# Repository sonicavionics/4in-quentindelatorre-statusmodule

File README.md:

# Quentin Dela Torre - Status Module

---

<div align="center">
  <div>

    <p><em>3D Render</em></p>
  </div>
  <br>

  <div>
    <br>
    <p><em>Schematic</em></p>
  </div>
  <br>
  
  <div>
    
    <br>
    <em>Footprint</em>
  </div>
</div>

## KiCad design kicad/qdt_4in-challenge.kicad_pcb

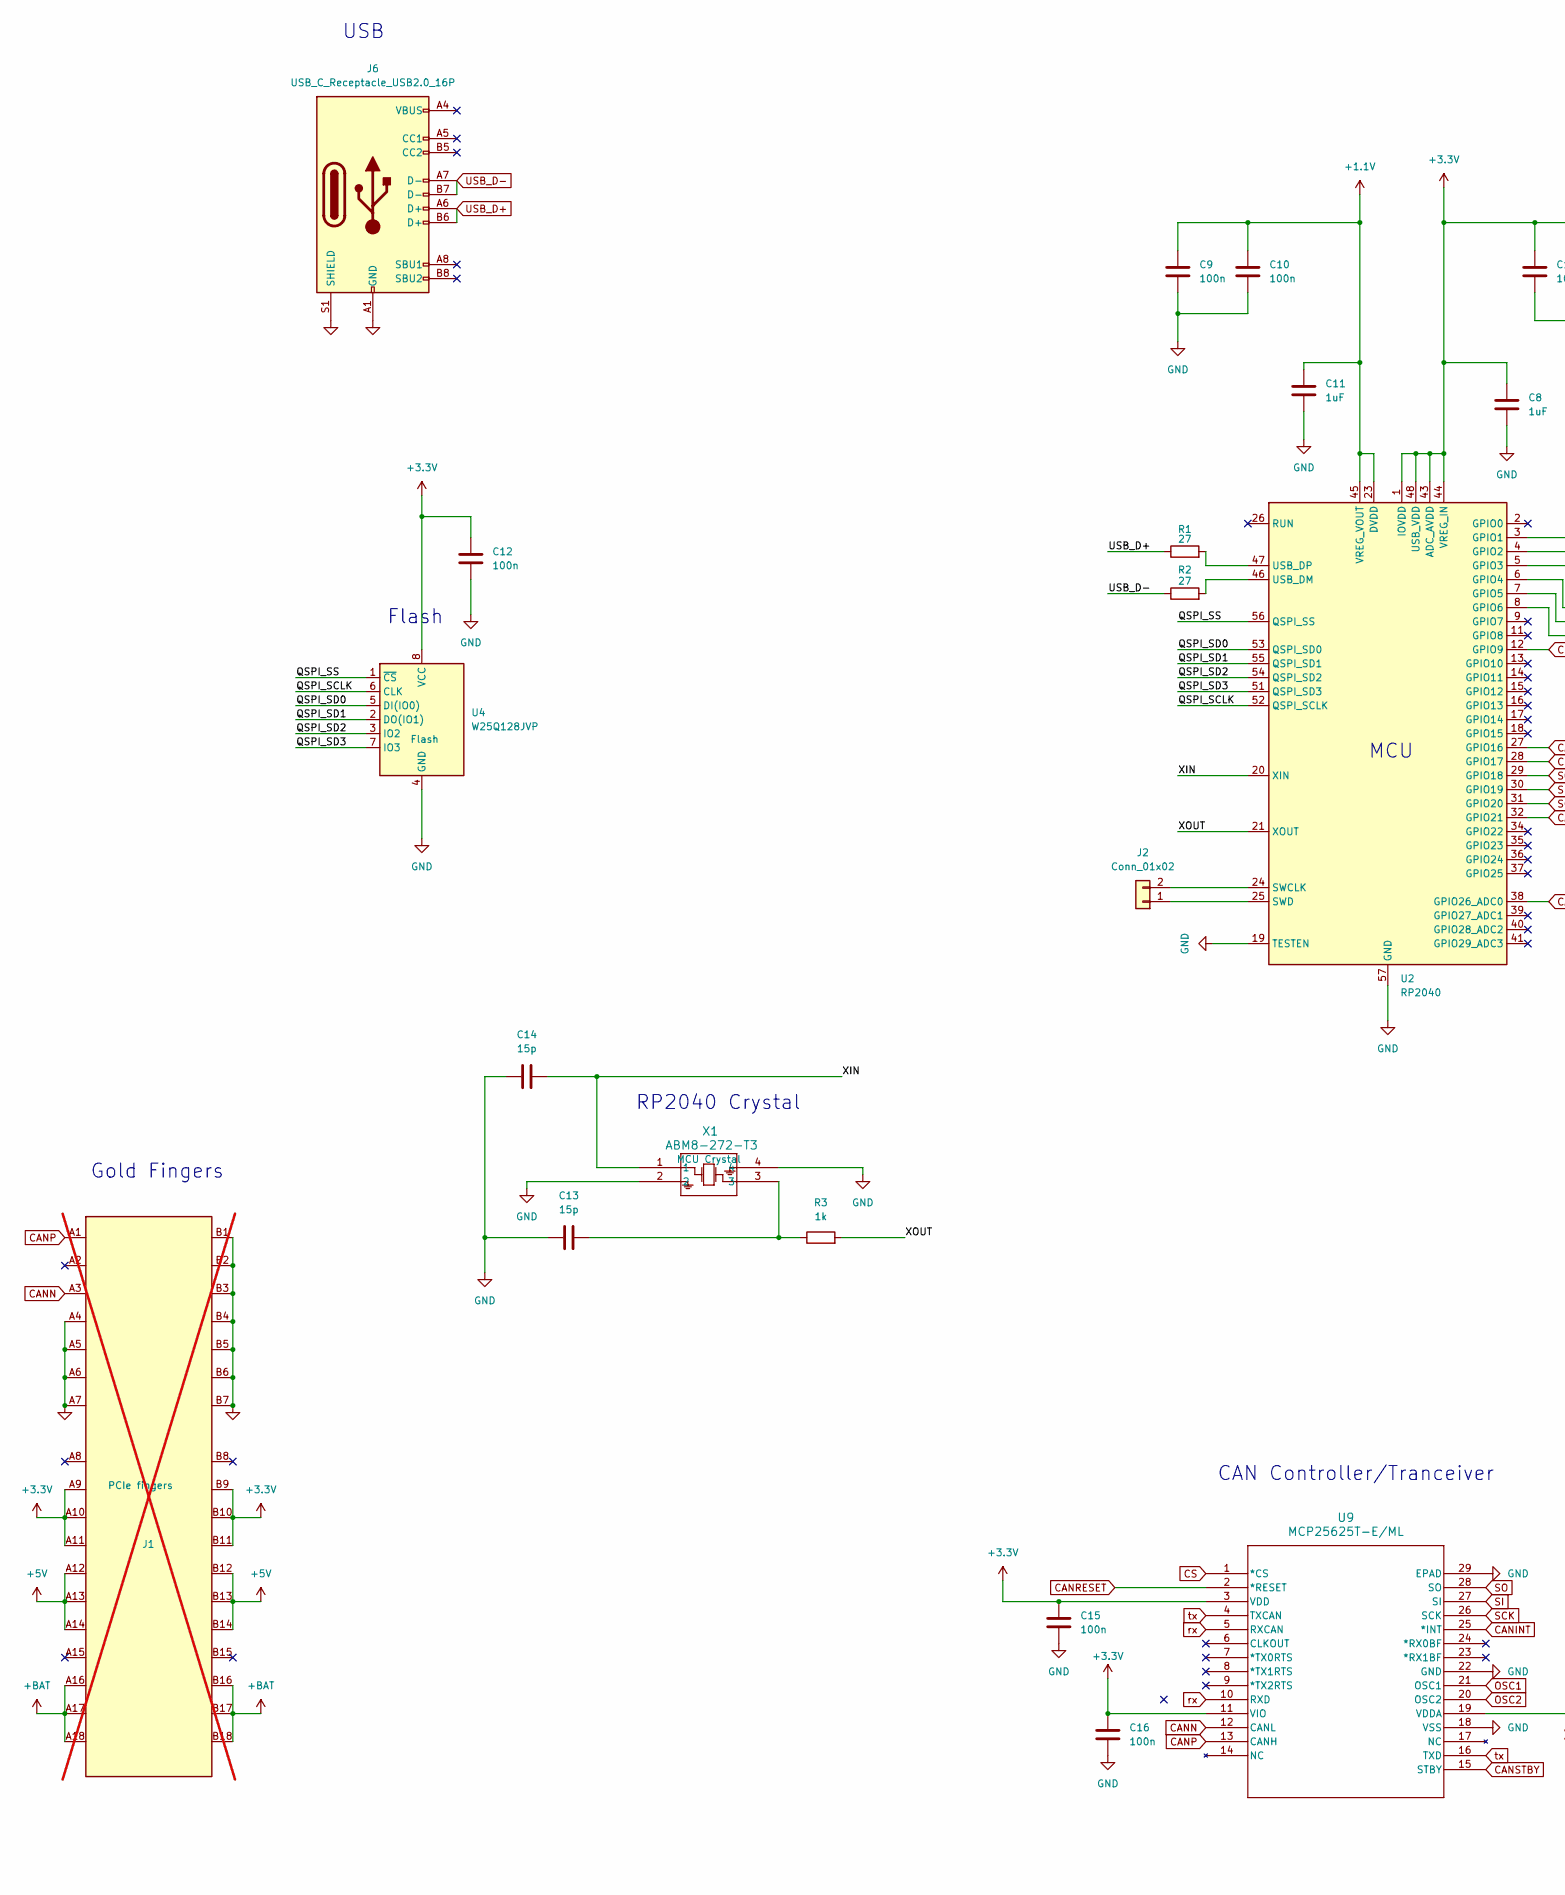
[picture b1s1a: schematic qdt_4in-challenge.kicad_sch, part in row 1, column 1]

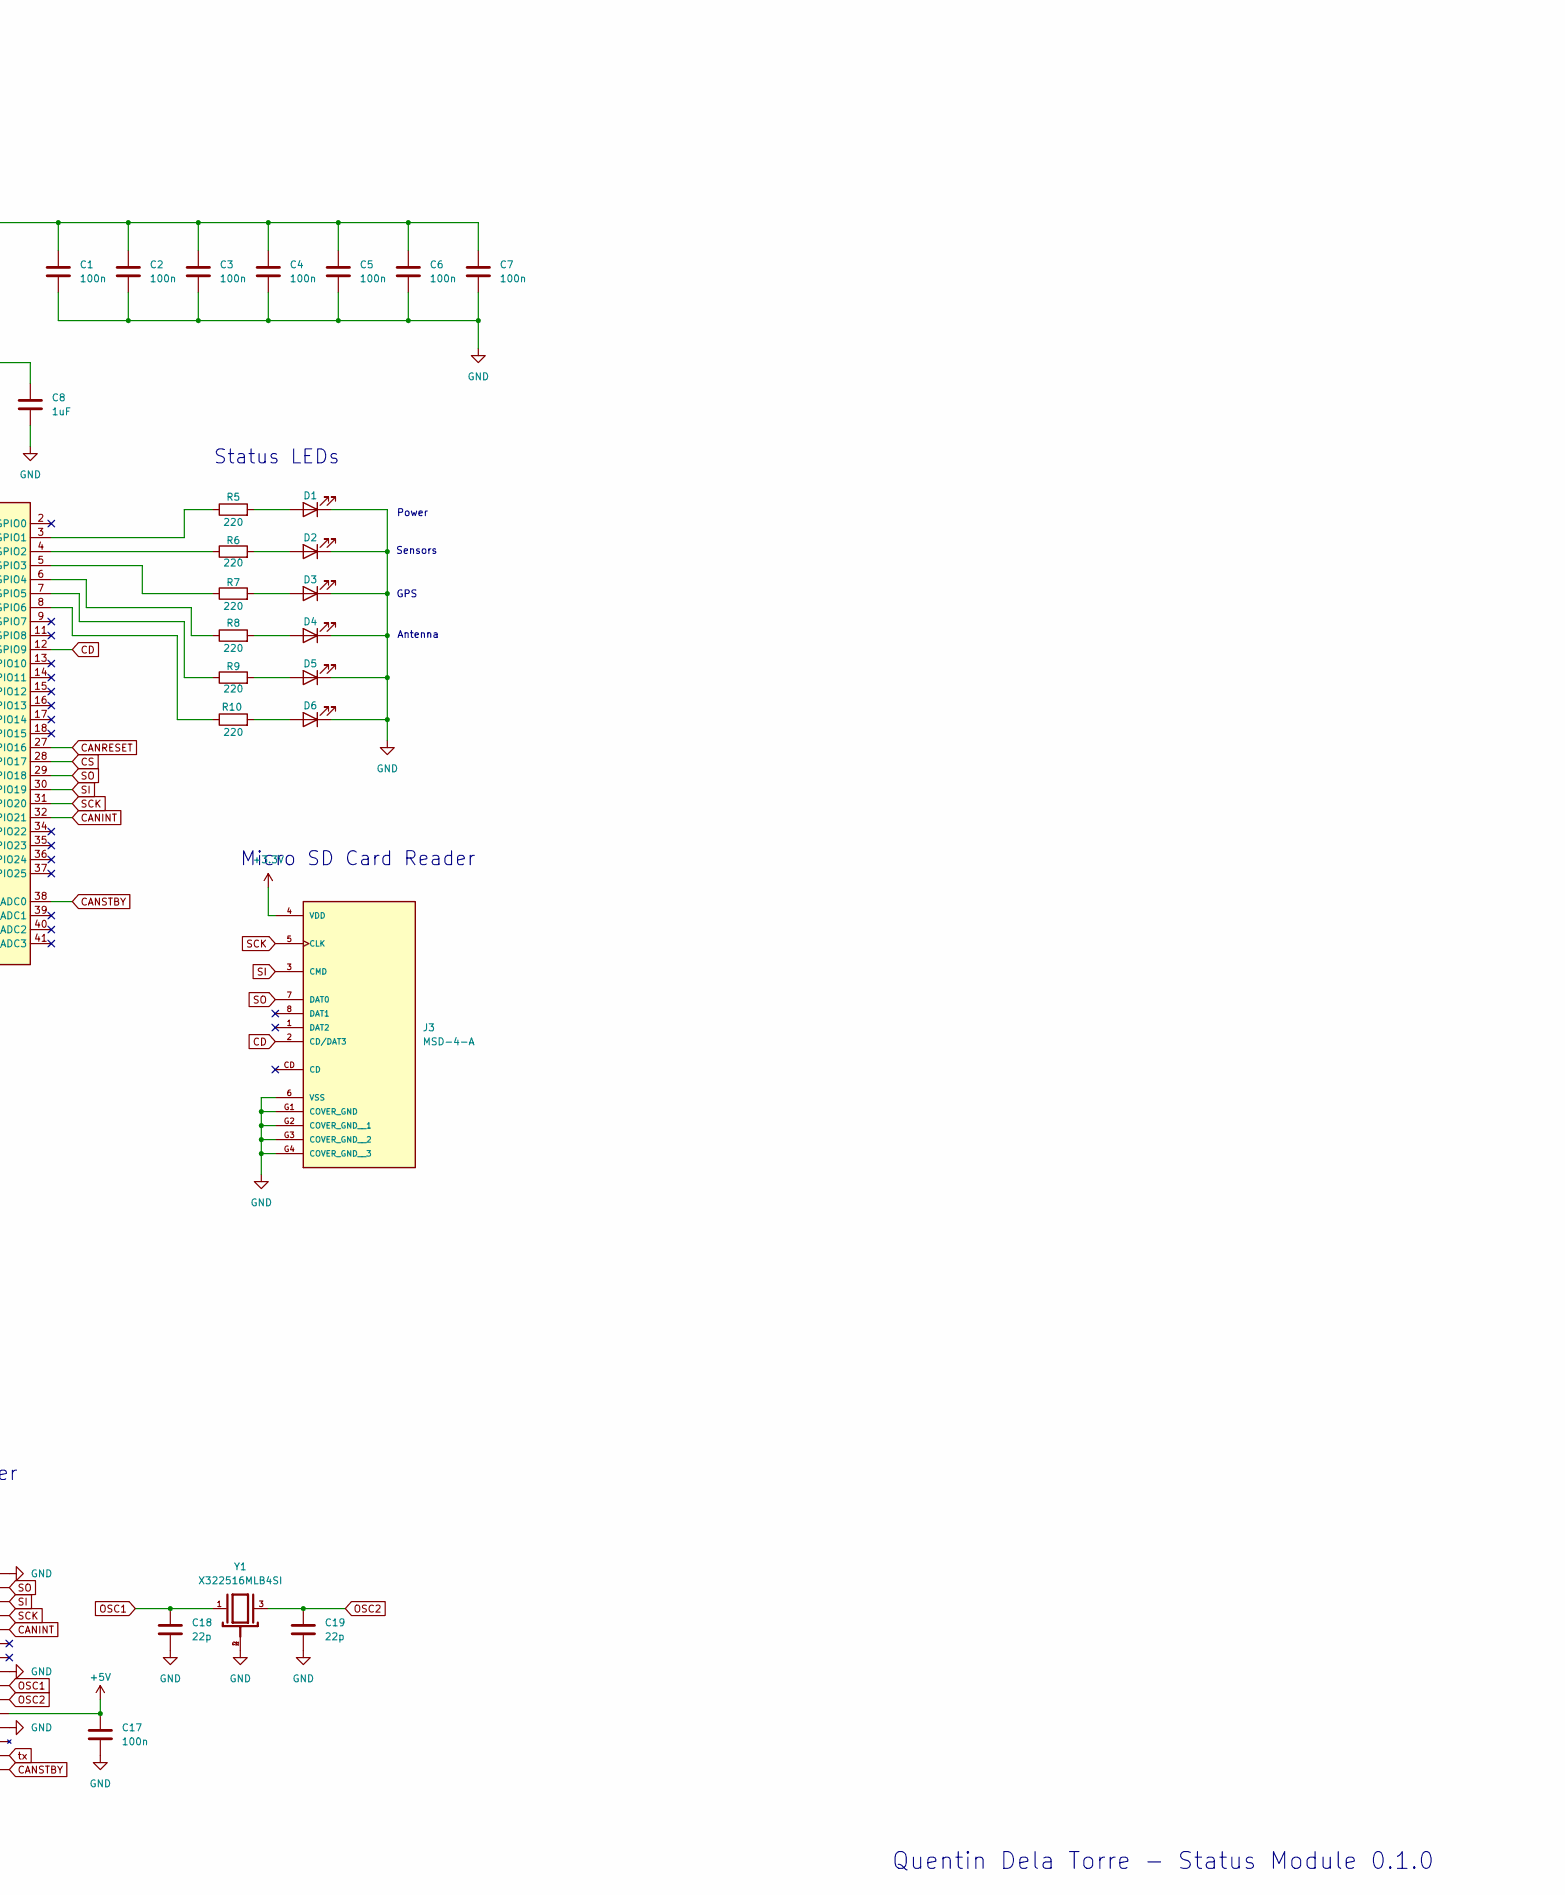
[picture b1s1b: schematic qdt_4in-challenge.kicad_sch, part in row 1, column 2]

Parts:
C1, C2, C3, C4, C5, C6, C7, C9, C10, C15, C16, C17: 100n; C_0402_1005Metric
C8, C11: 1uF; C_0402_1005Metric
C12: 100n; C_0603_1608Metric
C13, C14: 15p; C_0603_1608Metric
C18, C19: 22p; C_0603_1608Metric
D1, D2, D3, D4, D5, D6: LED; LED_0805_2012Metric
J1: Bus_PCI_Express_x1; BUS_PCIexpress_x1; LCSC Part # n/a; not fitted
J2: Conn_01x02; JST_EH_B2B-EH-A_1x02_P2.50mm_Vertical
J3: MSD-4-A; CUI_MSD-4-A; PARTREV 1.0
J6: USB_C_Receptacle_USB2.0_16P; USB_C_Receptacle_Palconn_UTC16-G; LCSC Part # C2765186
R1, R2: 27; R_0402_1005Metric
R3: 1k; R_0603_1608Metric
R5, R6, R7, R8, R9, R10: 220; R_0603_1608Metric
U2: RP2040; QFN-56-1EP_7x7mm_P0.4mm_EP3.2x3.2mm; LCSC C2040
U4: W25Q128JVP; WSON-8-1EP_6x5mm_P1.27mm_EP3.4x4.3mm; LCSC C190862
U9: MCP25625T-E/ML; QFN28_6X6MC_MCH; LCSC Part # C191253
X1: ABM8-272-T3; ABM8-272-T3_ABR; LCSC Part # C20625731
Y1: X322516MLB4SI; OSC_X322516MLB4SI; PARTREV N/A

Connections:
+1.1V: C9.1, C10.1, C11.1, U2.23 (DVDD), U2.45 (VREG_VOUT), U2.50 (DVDD)
+3.3V: C1.1, C2.1, C3.1, C4.1, C5.1, C6.1, C7.1, C8.1, C12.1, C15.1, C16.1, J1.A9 (+3.3V), J1.A10 (+3.3V), J1.A11 (~PERST), J1.B9 (JTAG1), J1.B10 (3.3Vaux), J1.B11 (~WAKE), J3.4 (VDD), U2.1 (IOVDD), U2.10 (IOVDD), U2.22 (IOVDD), U2.33 (IOVDD), U2.42 (IOVDD), U2.43 (ADC_AVDD), U2.44 (VREG_IN), U2.48 (USB_VDD), U2.49 (IOVDD), U4.8 (VCC), U9.3 (VDD), U9.11 (VIO)
+5V: C17.1, J1.A12 (GND), J1.A13 (REFCLK+), J1.A14 (REFCLK-), J1.B12 (RSVD), J1.B13 (GND), J1.B14 (PETp0), U9.19 (VDDA)
+BAT: J1.A16 (PERp0), J1.A17 (PERn0), J1.A18 (GND), J1.B16 (GND), J1.B17 (~PRSNT2), J1.B18 (GND)
/QSPI_SCLK: U2.52 (QSPI_SCLK), U4.6 (CLK)
/QSPI_SD0: U2.53 (QSPI_SD0), U4.5 (DI(IO0))
/QSPI_SD1: U2.55 (QSPI_SD1), U4.2 (DO(IO1))
/QSPI_SD2: U2.54 (QSPI_SD2), U4.3 (IO2)
/QSPI_SD3: U2.51 (QSPI_SD3), U4.7 (IO3)
/QSPI_SS: U2.56 (QSPI_SS), U4.1 (~CS)
/XIN: C14.2, U2.20 (XIN), X1.1
/XOUT: R3.2, U2.21 (XOUT)
CANINT: U2.32 (GPIO21), U9.25 (*INT)
CANN: J1.A3 (+12V), U9.12 (CANL)
CANP: J1.A1 (~PRSNT1), U9.13 (CANH)
CANRESET: U2.27 (GPIO16), U9.2 (*RESET)
CANSTBY: U2.38 (GPIO26_ADC0), U9.15 (STBY)
CD: J3.2 (CD/DAT3), U2.12 (GPIO9)
CS: U2.28 (GPIO17), U9.1 (*CS)
GND: C1.2, C2.2, C3.2, C4.2, C5.2, C6.2, C7.2, C8.2, C9.2, C10.2, C11.2, C12.2, C13.2, C14.1, C15.2, C16.2, C17.2, C18.2, C19.2, D1.1 (K), D2.1 (K), D3.1 (K), D4.1 (K), D5.1 (K), D6.1 (K), J1.A4 (GND), J1.A5 (JTAG2), J1.A6 (JTAG3), J1.A7 (JTAG4), J1.B1 (+12V), J1.B2 (+12V), J1.B3 (+12V), J1.B4 (GND), J1.B5 (SMCLK), J1.B6 (SMDAT), J1.B7 (GND), J3.6 (VSS), J3.G1 (COVER_GND), J3.G2 (COVER_GND__1), J3.G3 (COVER_GND__2), J3.G4 (COVER_GND__3), J6.A1 (GND), J6.A12 (GND), J6.B1 (GND), J6.B12 (GND), J6.S1 (SHIELD), U2.19 (TESTEN), U2.57 (GND), U4.4 (GND), U9.18 (VSS), U9.22 (GND), U9.29 (EPAD), X1.2, X1.4, Y1.2, Y1.4
unnamed: C13.1, R3.1, X1.3
unnamed: D1.2 (A), R5.2
unnamed: D2.2 (A), R6.2
unnamed: D3.2 (A), R7.2
unnamed: D4.2 (A), R8.2
unnamed: D5.2 (A), R9.2
unnamed: D6.2 (A), R10.2
unnamed: J2.1, U2.25 (SWD)
unnamed: J2.2, U2.24 (SWCLK)
unnamed: R5.1, U2.3 (GPIO1)
unnamed: R6.1, U2.4 (GPIO2)
unnamed: R7.1, U2.5 (GPIO3)
unnamed: R8.1, U2.6 (GPIO4)
unnamed: R9.1, U2.7 (GPIO5)
unnamed: R10.1, U2.8 (GPIO6)
unnamed: R2.2, U2.46 (USB_DM)
unnamed: R1.2, U2.47 (USB_DP)
OSC1: C18.1, U9.21 (OSC1), Y1.1
OSC2: C19.1, U9.20 (OSC2), Y1.3
SCK: J3.5 (CLK), U2.31 (GPIO20), U9.26 (SCK)
SI: J3.3 (CMD), U2.30 (GPIO19), U9.27 (SI)
SO: J3.7 (DAT0), U2.29 (GPIO18), U9.28 (SO)
USB_D+: J6.A6 (D+), J6.B6 (D+), R1.1
USB_D-: J6.A7 (D-), J6.B7 (D-), R2.1
rx: U9.5 (RXCAN), U9.10 (RXD)
tx: U9.4 (TXCAN), U9.16 (TXD)

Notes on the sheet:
Antenna
RP2040 Crystal
USB
Micro SD Card Reader
MCU
Sensors
Status LEDs
Quentin Dela Torre - Status Module 0.1.0
Gold Fingers
GPS
Power
CAN Controller/Tranceiver
Flash

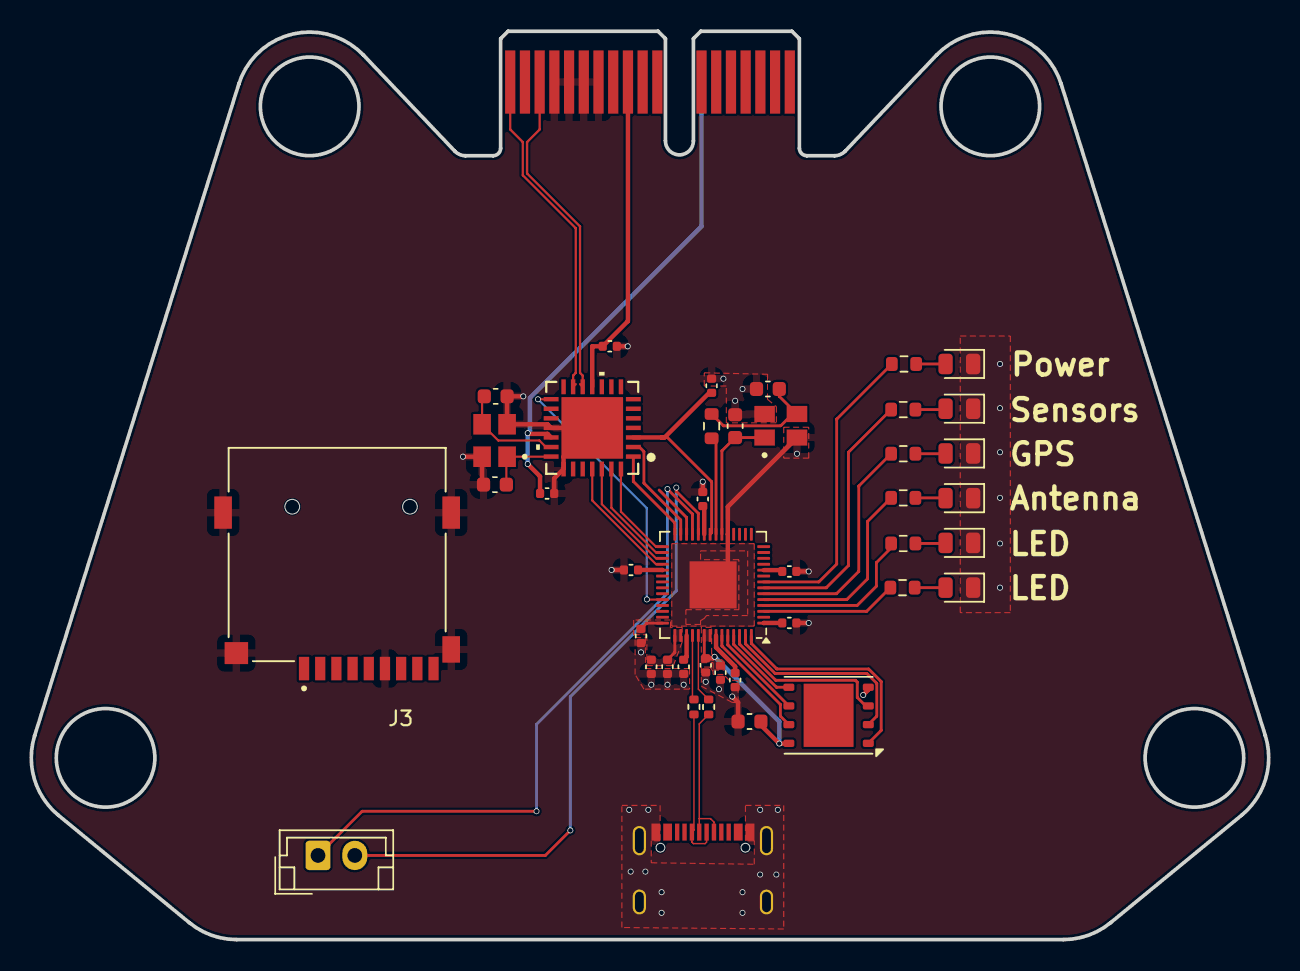
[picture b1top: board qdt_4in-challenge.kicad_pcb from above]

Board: 2 copper layers, 84.1 x 61.7 mm, 43 parts (1 on the bottom side), 46 nets.

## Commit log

2025-03-01 Update images
2025-03-03 Add LED array
2025-03-03 Remove files ending with :zone.Identifier
2025-03-03 Update file names and titles
2025-03-11 Moved components and removed buttons from pcb
2025-03-21 Update project
2025-05-06 Remove *.kicad_prl and add to gitignore
